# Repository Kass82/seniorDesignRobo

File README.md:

# seniorDesignRobo
Our little repo so we can test and document our work! :DD

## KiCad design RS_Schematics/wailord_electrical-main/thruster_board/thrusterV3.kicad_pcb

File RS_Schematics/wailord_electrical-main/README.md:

# RoboSubLA Wailord Electrical

## Team Leads
Katherine Bonomo & Andrew Ye

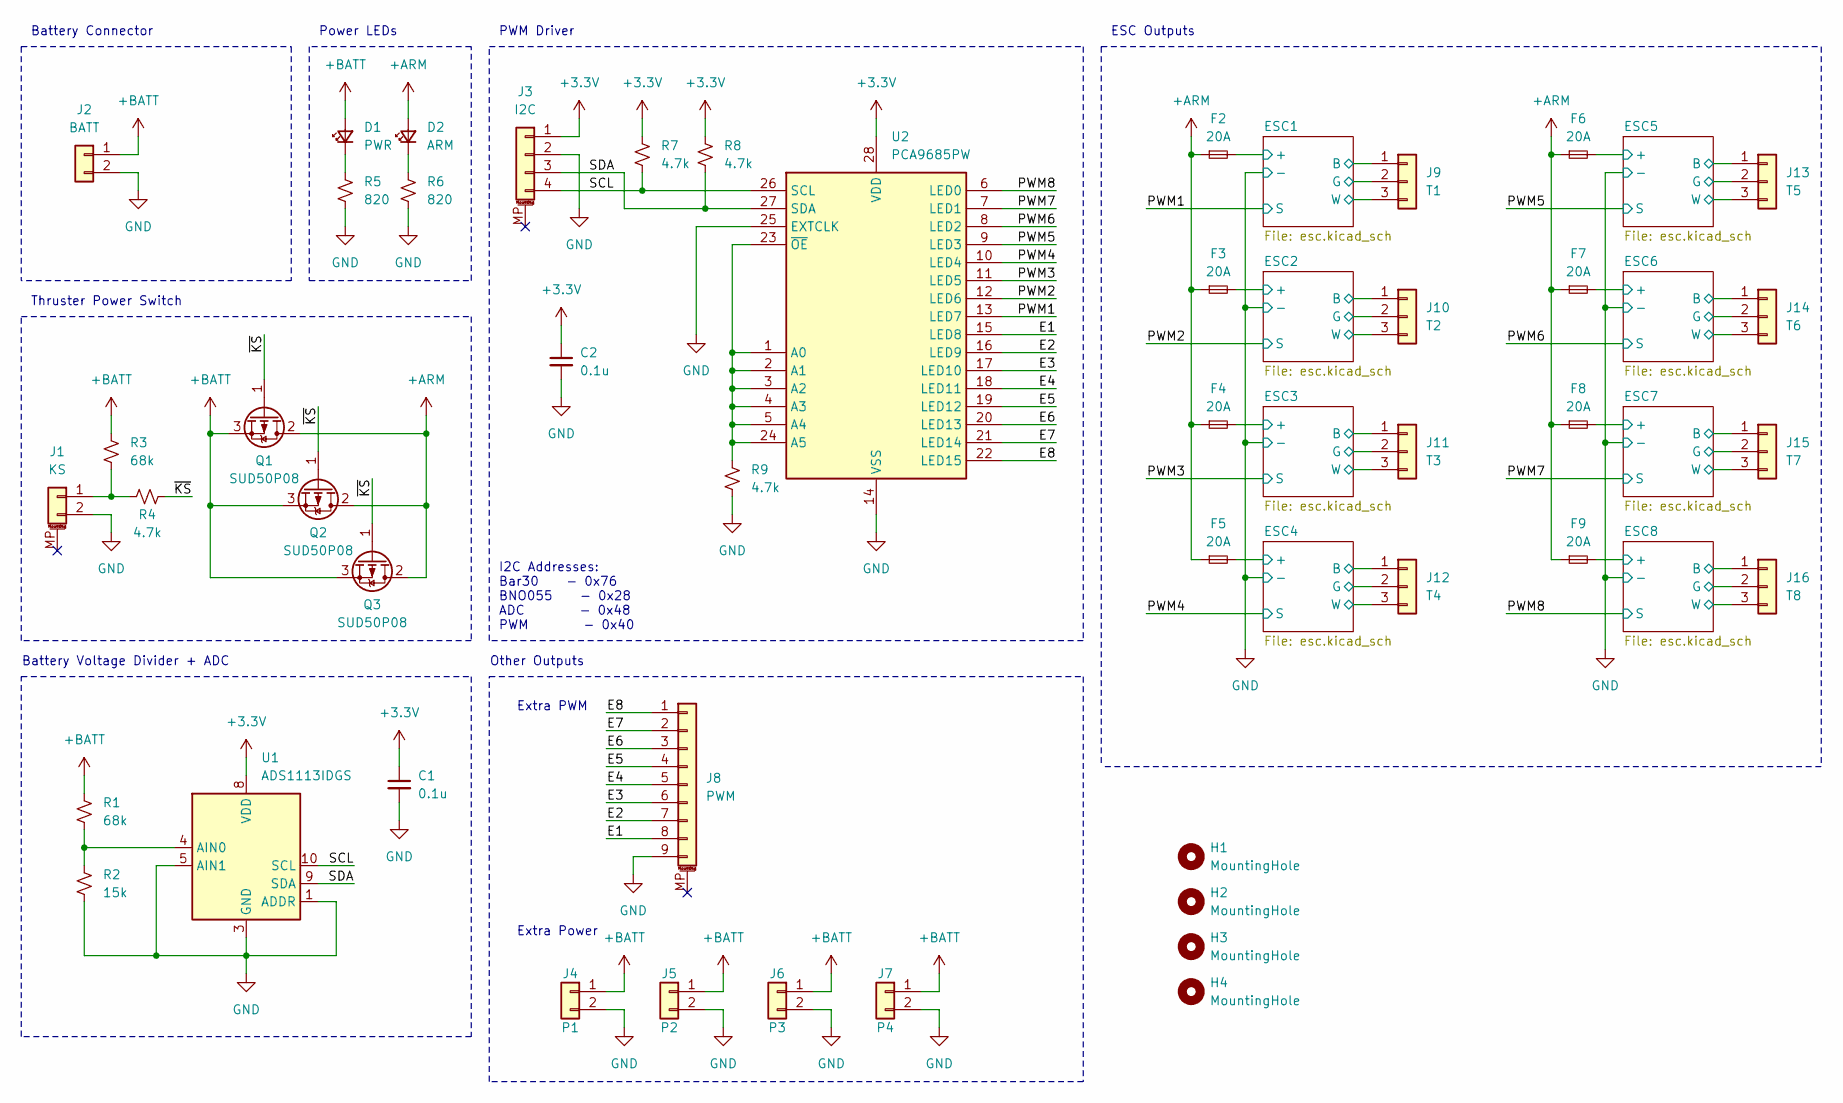
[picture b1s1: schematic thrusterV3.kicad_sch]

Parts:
C1, C2: 0.1u; C_0603_1608Metric_Pad1.08x0.95mm_HandSolder
D1: PWR; LED_0603_1608Metric_Pad1.05x0.95mm_HandSolder
D2: ARM; LED_0603_1608Metric_Pad1.05x0.95mm_HandSolder
F2, F3, F4, F5, F6, F7, F8, F9: 20A; Fuseholder_Blade_Mini_Keystone_3568
H1, H2, H3, H4: MountingHole; MountingHole_3.2mm_M3
J1: KS; JST_XH_B2B-XH-A_1x02_P2.50mm_Vertical
J2: BATT; XT90
J3: I2C; JST_GH_BM04B-GHS-TBT_1x04-1MP_P1.25mm_Vertical
J4: P1; JST_XH_B2B-XH-A_1x02_P2.50mm_Vertical
J5: P2; JST_XH_B2B-XH-A_1x02_P2.50mm_Vertical
J6: P3; JST_XH_B2B-XH-A_1x02_P2.50mm_Vertical
J7: P4; JST_XH_B2B-XH-A_1x02_P2.50mm_Vertical
J8: PWM; JST_GH_BM09B-GHS-TBT_1x09-1MP_P1.25mm_Vertical
J9: T1; Molex_KK-396_A-41791-0003_1x03_P3.96mm_Vertical
J10: T2; Molex_KK-396_A-41791-0003_1x03_P3.96mm_Vertical
J11: T3; Molex_KK-396_A-41791-0003_1x03_P3.96mm_Vertical
J12: T4; Molex_KK-396_A-41791-0003_1x03_P3.96mm_Vertical
J13: T5; Molex_KK-396_A-41791-0003_1x03_P3.96mm_Vertical
J14: T6; Molex_KK-396_A-41791-0003_1x03_P3.96mm_Vertical
J15: T7; Molex_KK-396_A-41791-0003_1x03_P3.96mm_Vertical
J16: T8; Molex_KK-396_A-41791-0003_1x03_P3.96mm_Vertical
Q1, Q2, Q3: SUD50P08; TO-252-2
R1, R3: 68k; R_0603_1608Metric_Pad0.98x0.95mm_HandSolder
R2: 15k; R_0603_1608Metric_Pad0.98x0.95mm_HandSolder
R4, R7, R8, R9: 4.7k; R_0603_1608Metric_Pad0.98x0.95mm_HandSolder
R5, R6: 820; R_0603_1608Metric_Pad0.98x0.95mm_HandSolder
U1: ADS1113IDGS; TSSOP-10_3x3mm_P0.5mm
U2: PCA9685PW; TSSOP-28_4.4x9.7mm_P0.65mm

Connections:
+3.3V: C1.1, C2.1, J3.1, R7.2, R8.2, U1.8 (VDD), U2.28 (VDD)
+ARM: D2.2 (A), F2.1, F3.1, F4.1, F5.1, F6.1, F7.1, F8.1, F9.1, Q1.2 (D), Q2.2 (D), Q3.2 (D)
+BATT: D1.2 (A), J2.1, J4.1, J5.1, J6.1, J7.1, Q1.3 (S), Q2.3 (S), Q3.3 (S), R1.1, R3.2
/E1: J8.8, U2.15 (LED8)
/E2: J8.7, U2.16 (LED9)
/E3: J8.6, U2.17 (LED10)
/E4: J8.5, U2.18 (LED11)
/E5: J8.4, U2.19 (LED12)
/E6: J8.3, U2.20 (LED13)
/E7: J8.2, U2.21 (LED14)
/E8: J8.1, U2.22 (LED15)
/ESC1/+: F2.2; also elsewhere on the board
/ESC1/B: J9.1; also elsewhere on the board
/ESC1/G: J9.2; also elsewhere on the board
/ESC1/W: J9.3; also elsewhere on the board
/ESC2/+: F3.2; also elsewhere on the board
/ESC2/B: J10.1; also elsewhere on the board
/ESC2/G: J10.2; also elsewhere on the board
/ESC2/W: J10.3; also elsewhere on the board
/ESC3/+: F4.2; also elsewhere on the board
/ESC3/B: J11.1; also elsewhere on the board
/ESC3/G: J11.2; also elsewhere on the board
/ESC3/W: J11.3; also elsewhere on the board
/ESC4/+: F5.2; also elsewhere on the board
/ESC4/B: J12.1; also elsewhere on the board
/ESC4/G: J12.2; also elsewhere on the board
/ESC4/W: J12.3; also elsewhere on the board
/ESC5/+: F6.2; also elsewhere on the board
/ESC5/B: J13.1; also elsewhere on the board
/ESC5/G: J13.2; also elsewhere on the board
/ESC5/W: J13.3; also elsewhere on the board
/ESC6/+: F7.2; also elsewhere on the board
/ESC6/B: J14.1; also elsewhere on the board
/ESC6/G: J14.2; also elsewhere on the board
/ESC6/W: J14.3; also elsewhere on the board
/ESC7/+: F8.2; also elsewhere on the board
/ESC7/B: J15.1; also elsewhere on the board
/ESC7/G: J15.2; also elsewhere on the board
/ESC7/W: J15.3; also elsewhere on the board
/ESC8/+: F9.2; also elsewhere on the board
/ESC8/B: J16.1; also elsewhere on the board
/ESC8/G: J16.2; also elsewhere on the board
/ESC8/W: J16.3; also elsewhere on the board
/PWM1: U2.13 (LED7); also elsewhere on the board
/PWM2: U2.12 (LED6); also elsewhere on the board
/PWM3: U2.11 (LED5); also elsewhere on the board
/PWM4: U2.10 (LED4); also elsewhere on the board
/PWM5: U2.9 (LED3); also elsewhere on the board
/PWM6: U2.8 (LED2); also elsewhere on the board
/PWM7: U2.7 (LED1); also elsewhere on the board
/PWM8: U2.6 (LED0); also elsewhere on the board
/SCL: J3.4, R7.1, U1.10 (SCL), U2.26 (SCL)
/SDA: J3.3, R8.1, U1.9 (SDA), U2.27 (SDA)
/~KS: Q1.1 (G), Q2.1 (G), Q3.1 (G), R4.1
GND: C1.2, C2.2, J1.2, J2.2, J3.2, J4.2, J5.2, J6.2, J7.2, J8.9, R2.2, R5.2, R6.2, R9.2, U1.1 (ADDR), U1.3 (GND), U1.5 (AIN1), U2.14 (VSS), U2.25 (EXTCLK); also elsewhere on the board
unnamed: D1.1 (K), R5.1
unnamed: D2.1 (K), R6.1
unnamed: J1.1, R3.1, R4.2
unnamed: R1.2, R2.1, U1.4 (AIN0)
unnamed: R9.1, U2.1 (A0), U2.2 (A1), U2.3 (A2), U2.4 (A3), U2.5 (A4), U2.23 (~OE), U2.24 (A5)

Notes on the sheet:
Other Outputs
ESC Outputs
PWM Driver
Thruster Power Switch
Power LEDs
Battery Voltage Divider + ADC
I2C Addresses: Bar30 - 0x76 BNO055 - 0x28 ADC - 0x48 PWM - 0x40
Extra Power
Extra PWM
Battery Connector

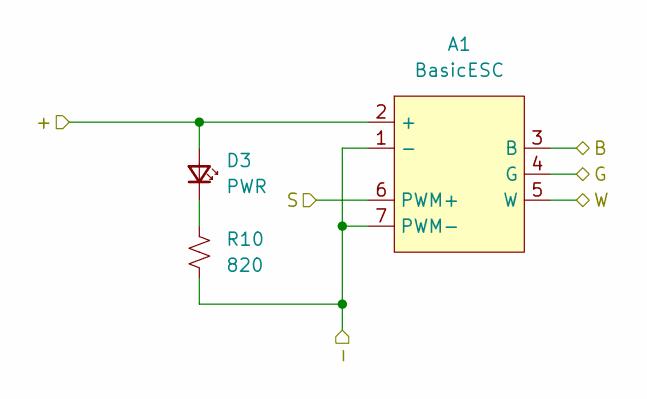
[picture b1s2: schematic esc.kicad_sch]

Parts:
A1: BasicESC
D3: PWR; LED_0603_1608Metric_Pad1.05x0.95mm_HandSolder
R10: 820; R_0603_1608Metric_Pad0.98x0.95mm_HandSolder

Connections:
/ESC1/+: A1.2 (+), D3.2 (A); also elsewhere on the board
/ESC1/B: A1.3 (B); also elsewhere on the board
/ESC1/G: A1.4 (G); also elsewhere on the board
/ESC1/W: A1.5 (W); also elsewhere on the board
/PWM1: A1.6 (PWM+); also elsewhere on the board
GND: A1.1 (-), A1.7 (PWM-), R10.1; also elsewhere on the board
unnamed: D3.1 (K), R10.2

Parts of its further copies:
A2, A3, A4, A5, A6, A7, A8: BasicESC
D4, D5, D6, D7, D8, D9, D10: PWR; LED_0603_1608Metric_Pad1.05x0.95mm_HandSolder
R11, R12, R13, R14, R15, R16, R17: 820; R_0603_1608Metric_Pad0.98x0.95mm_HandSolder

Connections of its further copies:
/ESC2/+: A2.2 (+), D4.2 (A); also elsewhere on the board
/ESC2/B: A2.3 (B); also elsewhere on the board
/ESC2/G: A2.4 (G); also elsewhere on the board
/ESC2/W: A2.5 (W); also elsewhere on the board
/ESC3/+: A3.2 (+), D5.2 (A); also elsewhere on the board
/ESC3/B: A3.3 (B); also elsewhere on the board
/ESC3/G: A3.4 (G); also elsewhere on the board
/ESC3/W: A3.5 (W); also elsewhere on the board
/ESC4/+: A4.2 (+), D6.2 (A); also elsewhere on the board
/ESC4/B: A4.3 (B); also elsewhere on the board
/ESC4/G: A4.4 (G); also elsewhere on the board
/ESC4/W: A4.5 (W); also elsewhere on the board
/ESC5/+: A5.2 (+), D7.2 (A); also elsewhere on the board
/ESC5/B: A5.3 (B); also elsewhere on the board
/ESC5/G: A5.4 (G); also elsewhere on the board
/ESC5/W: A5.5 (W); also elsewhere on the board
/ESC6/+: A6.2 (+), D8.2 (A); also elsewhere on the board
/ESC6/B: A6.3 (B); also elsewhere on the board
/ESC6/G: A6.4 (G); also elsewhere on the board
/ESC6/W: A6.5 (W); also elsewhere on the board
/ESC7/+: A7.2 (+), D9.2 (A); also elsewhere on the board
/ESC7/B: A7.3 (B); also elsewhere on the board
/ESC7/G: A7.4 (G); also elsewhere on the board
/ESC7/W: A7.5 (W); also elsewhere on the board
/ESC8/+: A8.2 (+), D10.2 (A); also elsewhere on the board
/ESC8/B: A8.3 (B); also elsewhere on the board
/ESC8/G: A8.4 (G); also elsewhere on the board
/ESC8/W: A8.5 (W); also elsewhere on the board
/PWM2: A2.6 (PWM+); also elsewhere on the board
/PWM3: A3.6 (PWM+); also elsewhere on the board
/PWM4: A4.6 (PWM+); also elsewhere on the board
/PWM5: A5.6 (PWM+); also elsewhere on the board
/PWM6: A6.6 (PWM+); also elsewhere on the board
/PWM7: A7.6 (PWM+); also elsewhere on the board
/PWM8: A8.6 (PWM+); also elsewhere on the board
GND: A2.1 (-), A2.7 (PWM-), A3.1 (-), A3.7 (PWM-), A4.1 (-), A4.7 (PWM-), A5.1 (-), A5.7 (PWM-), A6.1 (-), A6.7 (PWM-), A7.1 (-), A7.7 (PWM-), A8.1 (-), A8.7 (PWM-), R11.1, R12.1, R13.1, R14.1, R15.1, R16.1, R17.1; also elsewhere on the board
unnamed: D4.1 (K), R11.2
unnamed: D5.1 (K), R12.2
unnamed: D6.1 (K), R13.2
unnamed: D7.1 (K), R14.2
unnamed: D8.1 (K), R15.2
unnamed: D9.1 (K), R16.2
unnamed: D10.1 (K), R17.2

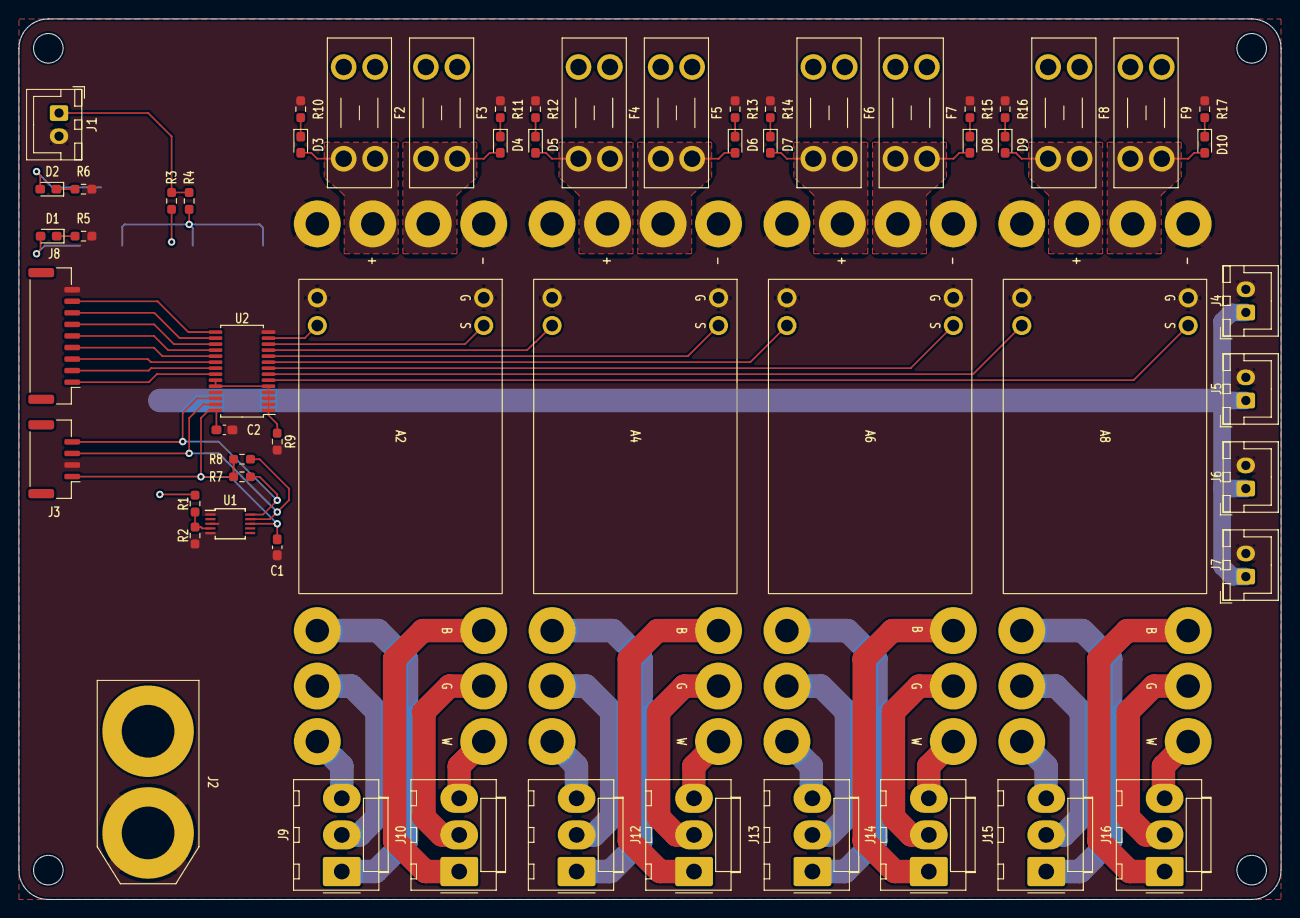
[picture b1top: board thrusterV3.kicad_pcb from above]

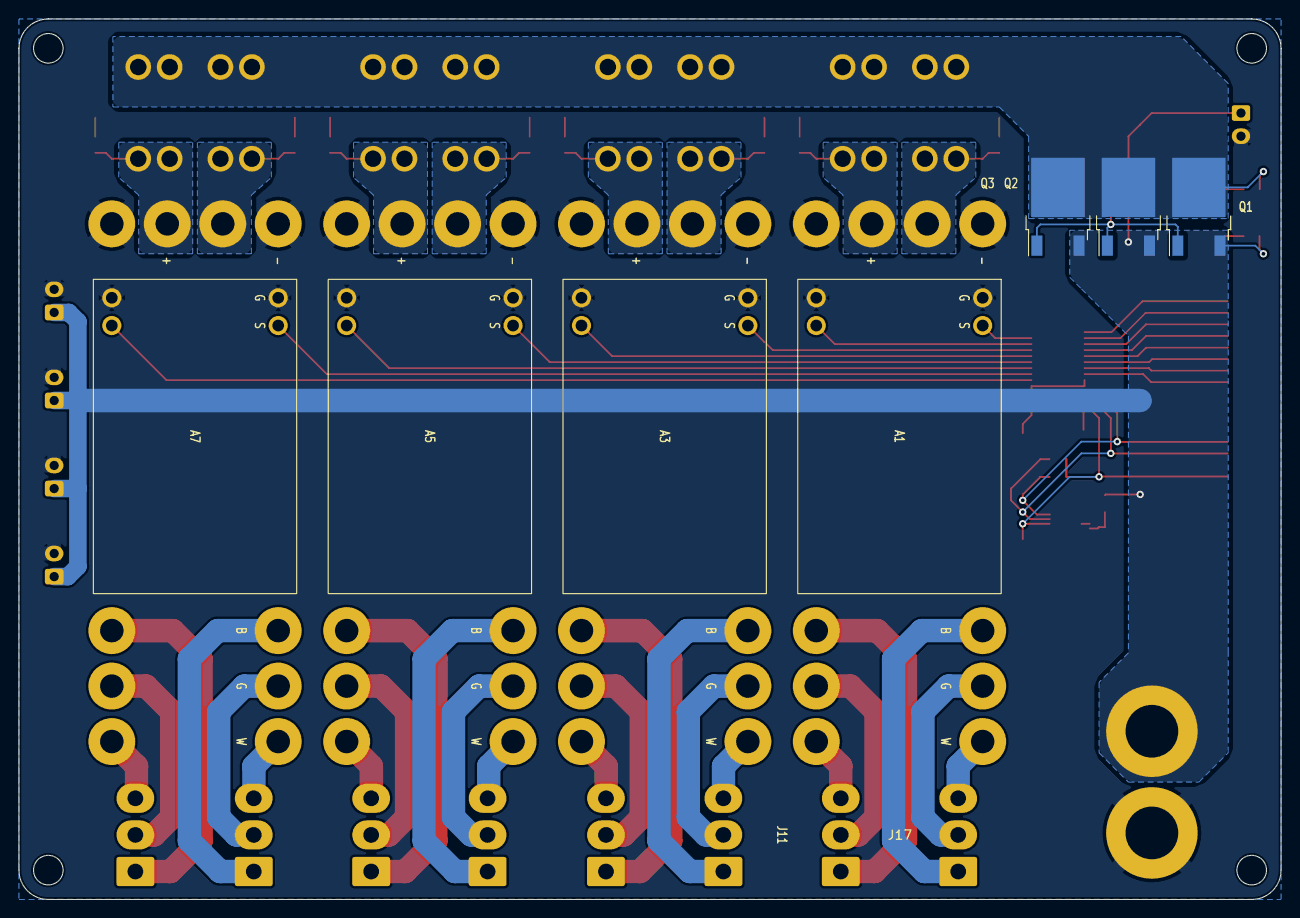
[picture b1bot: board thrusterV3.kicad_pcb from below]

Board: 4 copper layers, 136.5 x 95.3 mm, 70 parts (7 on the bottom side), 68 nets.

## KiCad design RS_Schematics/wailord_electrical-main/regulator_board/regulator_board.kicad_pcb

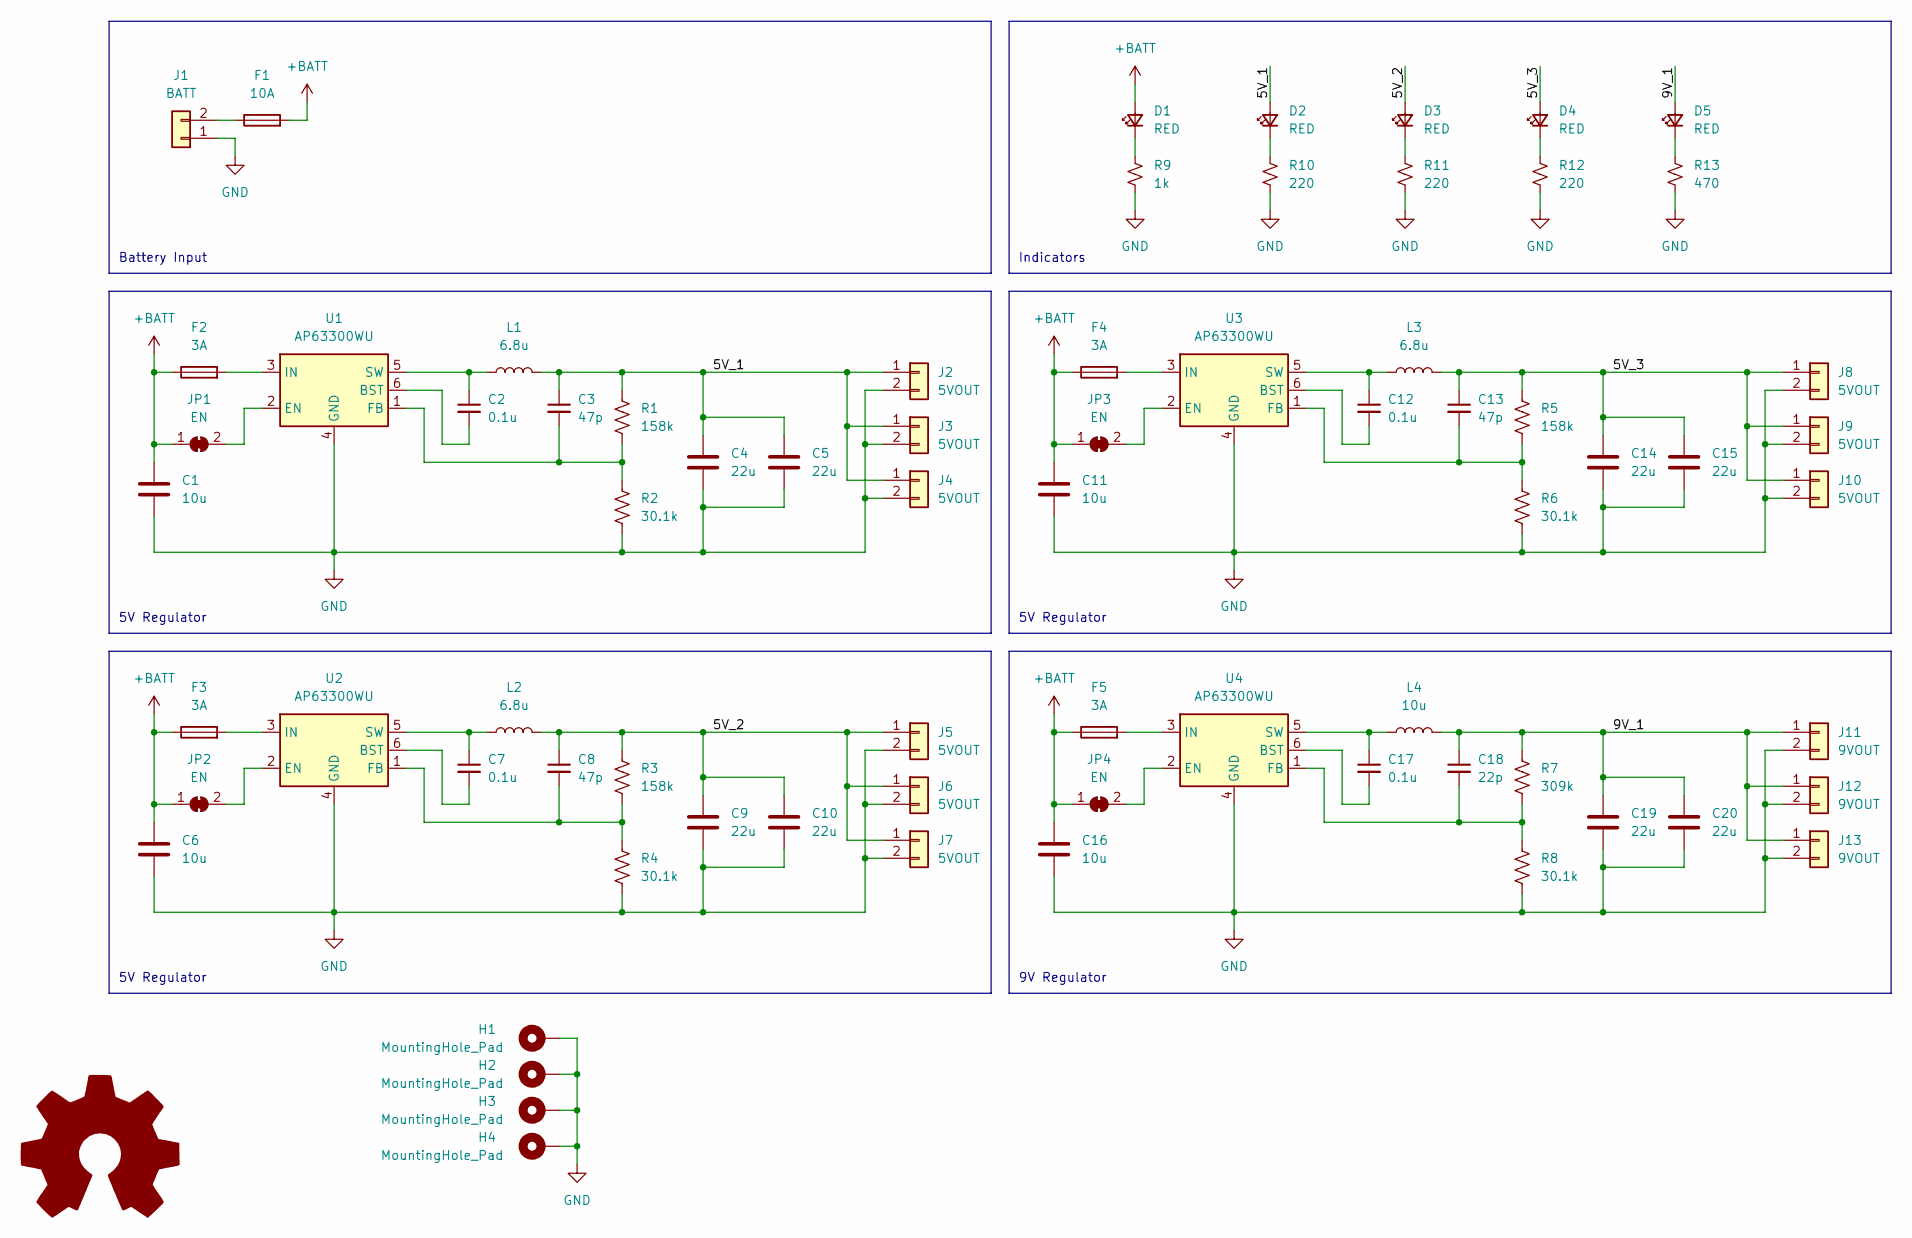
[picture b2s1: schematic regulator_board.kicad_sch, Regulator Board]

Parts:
C1, C6, C11, C16: 10u; C_0603_1608Metric_Pad1.08x0.95mm_HandSolder
C2, C7, C12, C17: 0.1u; C_0603_1608Metric_Pad1.08x0.95mm_HandSolder
C3, C8, C13: 47p; C_0603_1608Metric_Pad1.08x0.95mm_HandSolder
C4, C5, C9, C10, C14, C15, C19, C20: 22u; C_0603_1608Metric_Pad1.08x0.95mm_HandSolder
C18: 22p; C_0603_1608Metric_Pad1.08x0.95mm_HandSolder
D1, D2, D3, D4, D5: RED; LED_0603_1608Metric_Pad1.05x0.95mm_HandSolder
F1: 10A; Fuseholder_Blade_Mini_Keystone_3568
F2, F3, F4, F5: 3A; Fuse_0603_1608Metric_Pad1.05x0.95mm_HandSolder
H1, H2, H3, H4: MountingHole_Pad; MountingHole_3.2mm_M3_Pad_Via
J1: BATT; AMASS_XT60-M_1x02_P7.20mm_Vertical
J2, J3, J4, J5, J6, J7, J8, J9, J10: 5VOUT; JST_XH_B2B-XH-A_1x02_P2.50mm_Vertical
J11, J12, J13: 9VOUT; JST_XH_B2B-XH-A_1x02_P2.50mm_Vertical
JP1, JP2, JP3, JP4: EN; SolderJumper-2_P1.3mm_Bridged_RoundedPad1.0x1.5mm
L1, L2, L3: 6.8u; L_Bourns_SRP6030
L4: 10u; L_Bourns_SRP6030
LOGO1: Logo_Open_Hardware_Large; OSHW-Logo2_9.8x8mm_SilkScreen
R1, R3, R5: 158k; R_0603_1608Metric_Pad0.98x0.95mm_HandSolder
R2, R4, R6, R8: 30.1k; R_0603_1608Metric_Pad0.98x0.95mm_HandSolder
R7: 309k; R_0603_1608Metric_Pad0.98x0.95mm_HandSolder
R9: 1k; R_0603_1608Metric_Pad0.98x0.95mm_HandSolder
R10, R11, R12: 220; R_0603_1608Metric_Pad0.98x0.95mm_HandSolder
R13: 470; R_0603_1608Metric_Pad0.98x0.95mm_HandSolder
U1, U2, U3, U4: AP63300WU; TSOT-23-6

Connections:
+BATT: C1.1, C6.1, C11.1, C16.1, D1.2 (A), F1.2, F2.1, F3.1, F4.1, F5.1, JP1.1 (A), JP2.1 (A), JP3.1 (A), JP4.1 (A)
/5V_1: C3.1, C4.1, C5.1, D2.2 (A), J2.1, J3.1, J4.1, L1.2, R1.1
/5V_2: C8.1, C9.1, C10.1, D3.2 (A), J5.1, J6.1, J7.1, L2.2, R3.1
/5V_3: C13.1, C14.1, C15.1, D4.2 (A), J8.1, J9.1, J10.1, L3.2, R5.1
/9V_1: C18.1, C19.1, C20.1, D5.2 (A), J11.1, J12.1, J13.1, L4.2, R7.1
GND: C1.2, C4.2, C5.2, C6.2, C9.2, C10.2, C11.2, C14.2, C15.2, C16.2, C19.2, C20.2, H1.1, H2.1, H3.1, H4.1, J1.1, J2.2, J3.2, J4.2, J5.2, J6.2, J7.2, J8.2, J9.2, J10.2, J11.2, J12.2, J13.2, R2.2, R4.2, R6.2, R8.2, R9.2, R10.2, R11.2, R12.2, R13.2, U1.4 (GND), U2.4 (GND), U3.4 (GND), U4.4 (GND)
unnamed: C2.1, L1.1, U1.5 (SW)
unnamed: C2.2, U1.6 (BST)
unnamed: C3.2, R1.2, R2.1, U1.1 (FB)
unnamed: C7.1, L2.1, U2.5 (SW)
unnamed: C7.2, U2.6 (BST)
unnamed: C8.2, R3.2, R4.1, U2.1 (FB)
unnamed: C12.1, L3.1, U3.5 (SW)
unnamed: C12.2, U3.6 (BST)
unnamed: C13.2, R5.2, R6.1, U3.1 (FB)
unnamed: C17.1, L4.1, U4.5 (SW)
unnamed: C17.2, U4.6 (BST)
unnamed: C18.2, R7.2, R8.1, U4.1 (FB)
unnamed: D1.1 (K), R9.1
unnamed: D2.1 (K), R10.1
unnamed: D3.1 (K), R11.1
unnamed: D4.1 (K), R12.1
unnamed: D5.1 (K), R13.1
unnamed: F1.1, J1.2
unnamed: F2.2, U1.3 (IN)
unnamed: F3.2, U2.3 (IN)
unnamed: F4.2, U3.3 (IN)
unnamed: F5.2, U4.3 (IN)
unnamed: JP1.2 (B), U1.2 (EN)
unnamed: JP2.2 (B), U2.2 (EN)
unnamed: JP3.2 (B), U3.2 (EN)
unnamed: JP4.2 (B), U4.2 (EN)

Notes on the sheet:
Indicators
Battery Input
5V Regulator
9V Regulator

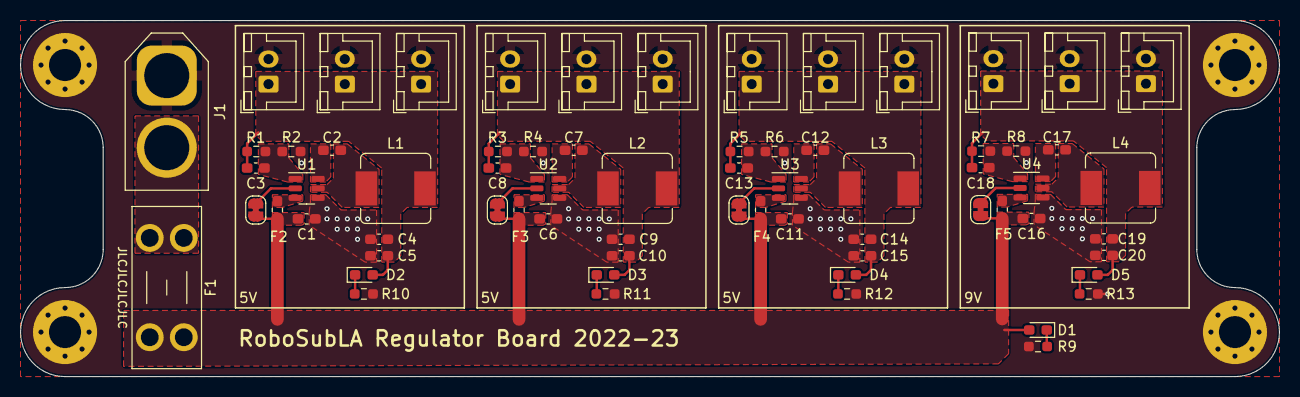
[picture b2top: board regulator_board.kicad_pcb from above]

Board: 2 copper layers, 125.7 x 35.6 mm, 73 parts (1 on the bottom side), 32 nets.

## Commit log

2025-10-31 Gerber Files all included
2026-03-04 Initial add notes
2026-03-04 Login
    Tutorial onto the server, BUT this is the root not the user accounts
2026-03-04 usr
    Here i focused on creating a user account that has access to it
2026-03-04 Create documentation
2026-03-04 http to https
    here i just set it up thru git bash after logging into the root and then just followed the steps listed! and i was able to get it to successfully change to https
    https://robosubla.org/
2026-03-04 More details to solidworks install
2026-03-06 Wailord model for unity
2026-03-07 My personal notes and a cleaned up version
    Notes up til now. I won't lie, it looks messy and felt like I kept doing work and researching and studying but cleaning up, feels like nothing was done
2026-03-07 Update notes on project progress and issues
2026-03-09 Document HTTP to HTTPS transition
    Added steps and notes for transitioning from HTTP to HTTPS, including firewall checks and Certbot usage for SSL certificate installation.
    ------
    notes on updating it
2026-03-09 http to https
    i had it in main but meant to upload it hereeee
    it's just getting it to become certified so it doesnt pop up as not secure when you're opening the link
2026-03-11 Everything I've worked on thus far sort of
2026-03-11 Update documentation
2026-03-11 Self Note Documentation
2026-03-11 Adding Nvidia Orin Nano related items
2026-03-11 Notes Folders added for the team
2026-03-11 Computer Vision stuff addded
2026-03-11 Adding Main.cpp
2026-03-12 Updated to main
2026-03-13 Adding Items that weren't initially ported over
2026-03-17 Create README.md with initial development notes
    Added initial notes related to site development.
2026-03-18 Update Robosub documentation
2026-03-18 Rename Robosub Documentation..txt to Control Research & Documentation.txt
2026-03-18 Add simulation documentation
    Document progress on simulation development, including model importation, water physics setup, and thruster testing results.
2026-03-18 Document control research and Arduino project details
    Added detailed documentation on micro-ROS, Raspberry Pi Pico 2, Teensy 4.1, communication protocols, and Arduino-based robotic car project.
2026-03-18 Add simulation documentation
    Documented the progress and tests conducted on the submarine simulation, including thruster setups and results from various tests.
2026-03-19 Squashed commit of the following:
    commit 608241d3cdf7de955cb4a15d3df1498302ad9102
    Author: AlvinS2325 <asun13@calstatela.edu>
    Date: Wed Mar 18 00:45:09 2026 -0700
    Add simulation documentation
    Documented the progress and tests conducted on the submarine simulation, including thruster setups and results from various tests.
    commit 0165ee637c6205b5cda871673cdf2fd9db760d7c
2026-03-19 move notes
2026-03-19 move notes part 2
2026-03-20 Revise RoboSub contribution documentation
    Updated the RoboSub contribution documentation to include details on sonar research, control logic, simulation transition, and current technical issues.
2026-03-20 Revise RoboSub documentation with latest updates
    Updated the RoboSub contribution documentation to include recent developments in sonar research, control logic, simulation work, and current technical issues faced during the project.
2026-03-23 Config Updates
2026-03-25 Revise RoboSub contribution documentation
    Updated the RoboSub contribution documentation with detailed sections on sonar research, control logic, simulation work, and current technical issues faced.
2026-03-25 Update simulation documentation with test results
    Documented the results and findings from various submarine thruster tests, including horizontal and vertical thruster performance, yaw control, and input system setup. Summarized the current status a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
2026-03-25 Create front
2026-03-25 Create hello
2026-03-25 Create ge
2026-03-27 Documentation
2026-04-23 notes
    Using the nginx config to remove .html when opening/loading a new page
2026-04-23 notes
    from my branch
2026-04-24 Up-to-Date
    - Added Google Colab .ipynb trials and final working version
    - Updated working notes to include what happened in the timeskip
    - Updated links to include a very important link
